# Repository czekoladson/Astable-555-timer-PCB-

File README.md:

Projekt płytki pcb z układem cyfrowym N555. (Polega na tym ,że zależnie w którą stronę przekręcisz potencjometr to dioda LED miga wolniej lub szybciej.)

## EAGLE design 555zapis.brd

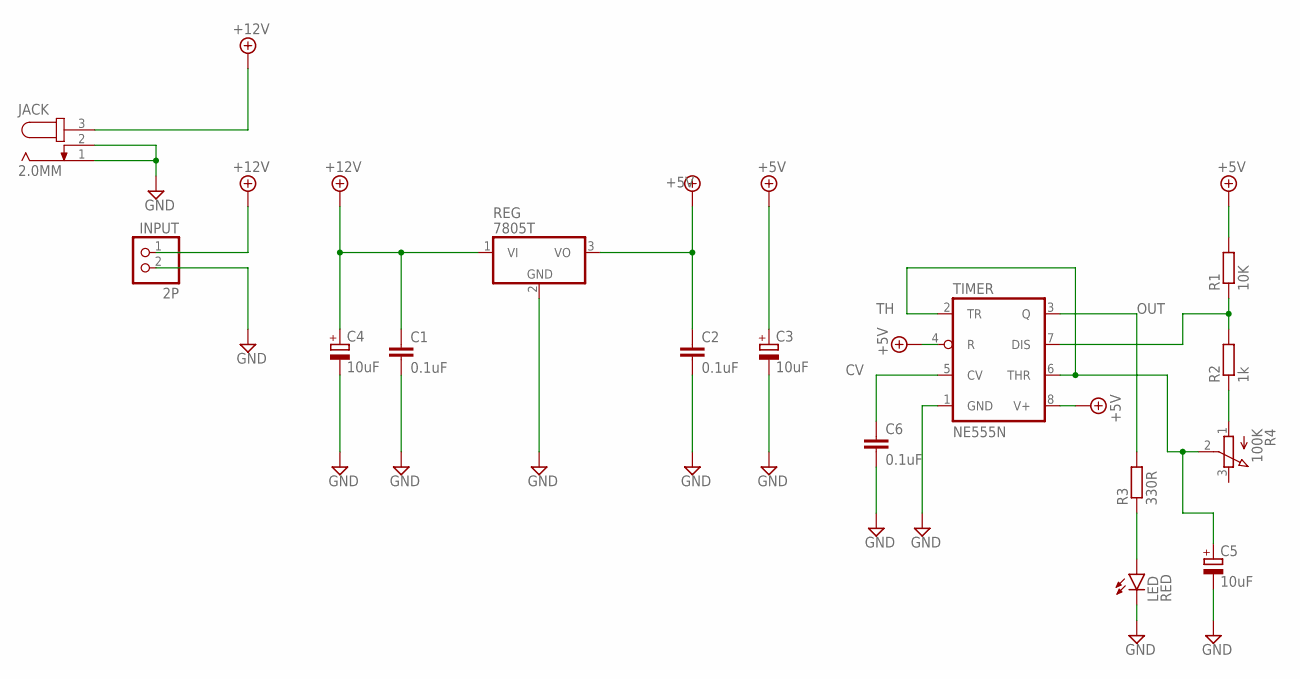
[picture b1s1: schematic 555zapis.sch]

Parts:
C1, C2, C6: 0.1uF; C050-030X075
C3, C4, C5: 10uF; E3,5-8
INPUT: 2P; 1X02
JACK: 2.0MM; SPC4078
LED: RED; LED5MM
R1: 10K; 0207/10
R2: 1k; 0207/10
R3: 330R; 0207/10
R4: 100K; 3RP/1610N
REG: 7805T; TO220H
TIMER: NE555N; DIL08

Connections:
+5V: C2.1, C3.+, R1.2, REG.3 (VO), TIMER.4 (R), TIMER.8 (V+)
+12V: C1.1, C4.+, INPUT.1, JACK.3, REG.1 (VI)
CV: C6.1, TIMER.5 (CV)
GND: C1.2, C2.2, C3.-, C4.-, C5.-, C6.2, INPUT.2, JACK.1, JACK.2, LED.K (C), REG.2 (GND), TIMER.1 (GND)
unnamed: R2.1, R4.1 (A)
unnamed: R1.1, R2.2, TIMER.7 (DIS)
unnamed: LED.A, R3.1
OUT: R3.2, TIMER.3 (Q)
TH: C5.+, R4.2 (S), TIMER.2 (TR), TIMER.6 (THR)

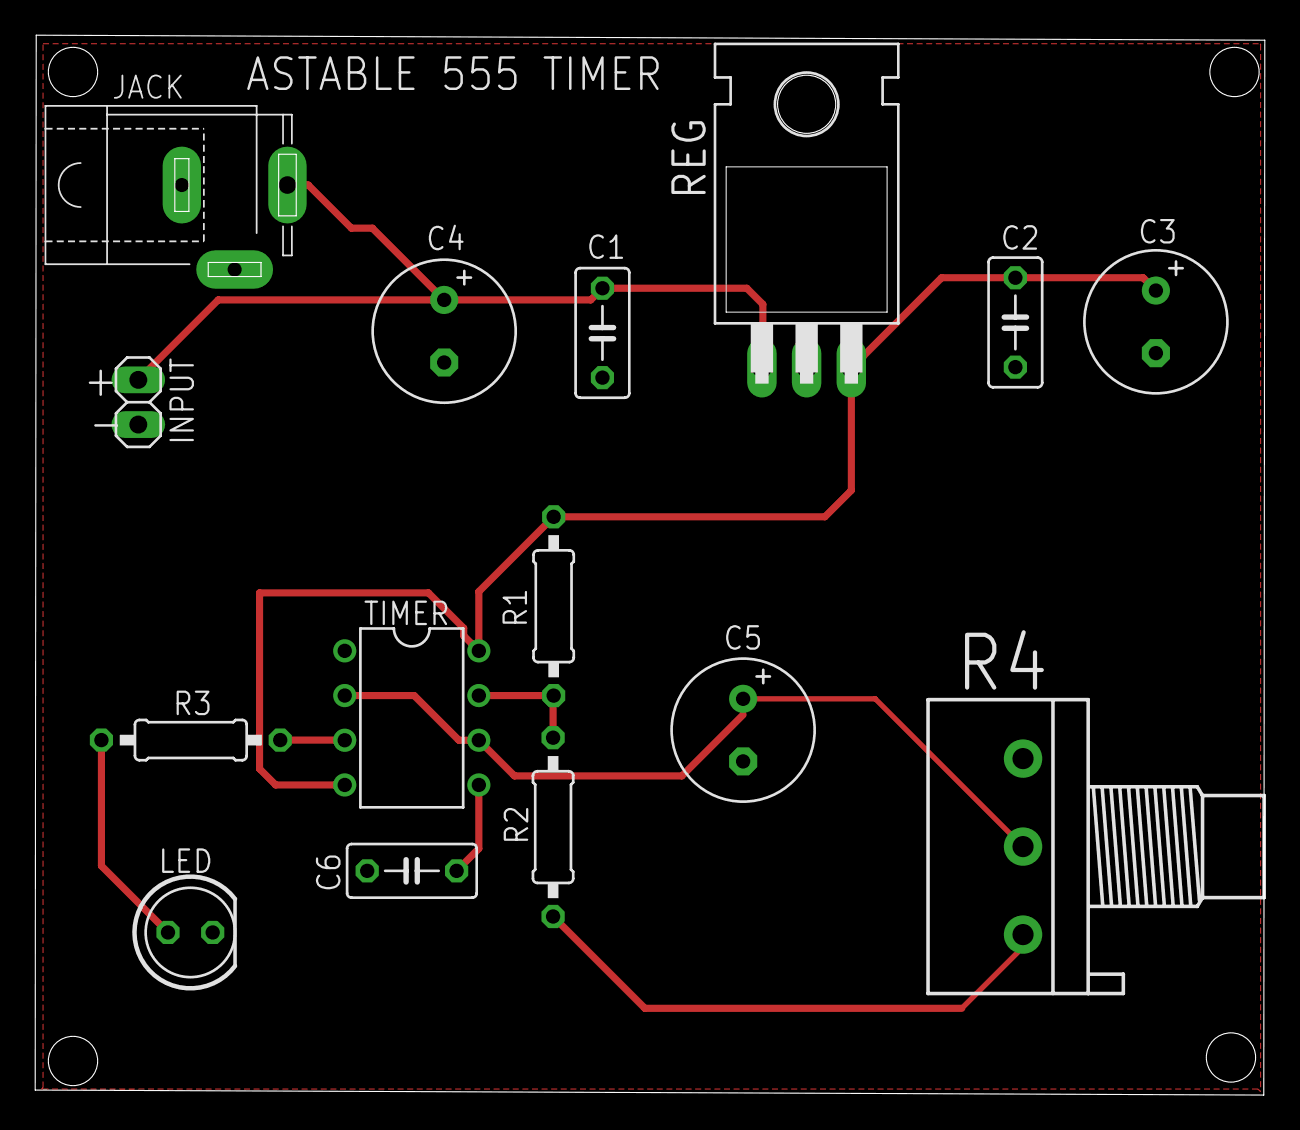
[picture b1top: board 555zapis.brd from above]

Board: 2 copper layers, 69.9 x 60.2 mm, 15 parts (0 on the bottom side), 9 nets.

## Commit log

2024-10-15 Dodany gotowy projekt płytki PCB
